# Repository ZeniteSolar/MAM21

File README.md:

# MAM21
**M**ódulo de **A**cionamento do **M**otor 2021

Embarcação Guarapuvu II

Equipe Zênite Solar

### About
High current >150A Electronic Speed Controller for **[ME0909](https://www.electricmotorsport.com/me0909-pmdc-motor-12-48v-4-hp-cont-12-8-hp-pk.html)** motor, with CANBus.

### Images

### Sobre
Este módulo é responsável por realizar o acionamento de um motor de imã permanente, controlando sua velocidade e sentido de rotação.

### Requisitos de projeto

1. **Acionamento do motor**
   - Permitir o acionamento nos dois sentidos de rotação
   - Permitir o controle em malha fechada
     - Corrente/Torque
     - Tensão/RPM

2. **Proteções**
   - Sobre-temperatura do motor
   - Sobre-temperatura do acionamento
   - Sobre-tensão de entrada
   - Sobre-corrente de saída
   - Falha de comunicação
   - Desconexão dos mosfets de potência
     - Garantir que os mosfets permaneçam desligados se a placa de controle for removida
   - Lógica para início de funcionamento
     - O motor só pode ser acionado se o procedimento de início for seguido na sequência correta
       - Dead man`s switch conectado
       - Sistema elétrico ativado
       - Potenciômetro em zero
       - Chave do motor ligada

3. **Interfaces**
   - Ser controlado pela rede CANBUS implementada na embarcação
   - Sinalização por meio de LEDs
   - Permitir debug pela serial

### Abordagens

Especificações do conversor

| Tensão de Entrada | 20 ~ 60 V |
| ----------------: | :-------- |
|   Tensão de Saída | 0 ~ 48V   |
| Corrente de Saída | 150 A     |
|        Eficiência | > 80%     |

Dados os requisitos e especificações apresentadas anteriormente, foi definido que a topologia utilizada será um conversor ***chopper***, por não haver necessidade de elevação de tensão e por este permitir a variação da tensão média na carga mantendo uma boa eficiência. 

Em um motor DC, a inversão de seu sentido de rotação é feita com a inversão da polaridade, obtida conforme a lógica de acionamento das chaves da ponte H. Uma característica da ponte H completa é que além da inversão de polaridade é possível criar lógicas de acionamento para frear o motor. Importante lembrar que **AS CHAVES DO MESMO BRAÇO NUNCA DEVEM SER ACIONADAS AO MESMO TEMPO**, sob pena de destruição das chaves ou danos ao sistema elétrico da embarcação.

Para que seja possível o monitoramento dos parâmetros do motor e para fechar a malha de controle, precisarão ser empregados sensores para o monitoramento da corrente e rotação do motor. O diagrama abaixo apresenta a topologia utilizada para o acionamento.

O motor utilizado pela embarcação é o **[ME0909](https://www.electricmotorsport.com/me0909-pmdc-motor-12-48v-4-hp-cont-12-8-hp-pk.html)**. Este motor possui tensão de operação de 12 ~ 48V e 4,8 kW de potência nominal.

A rede CAN utilizada será a já implementada atualmente.

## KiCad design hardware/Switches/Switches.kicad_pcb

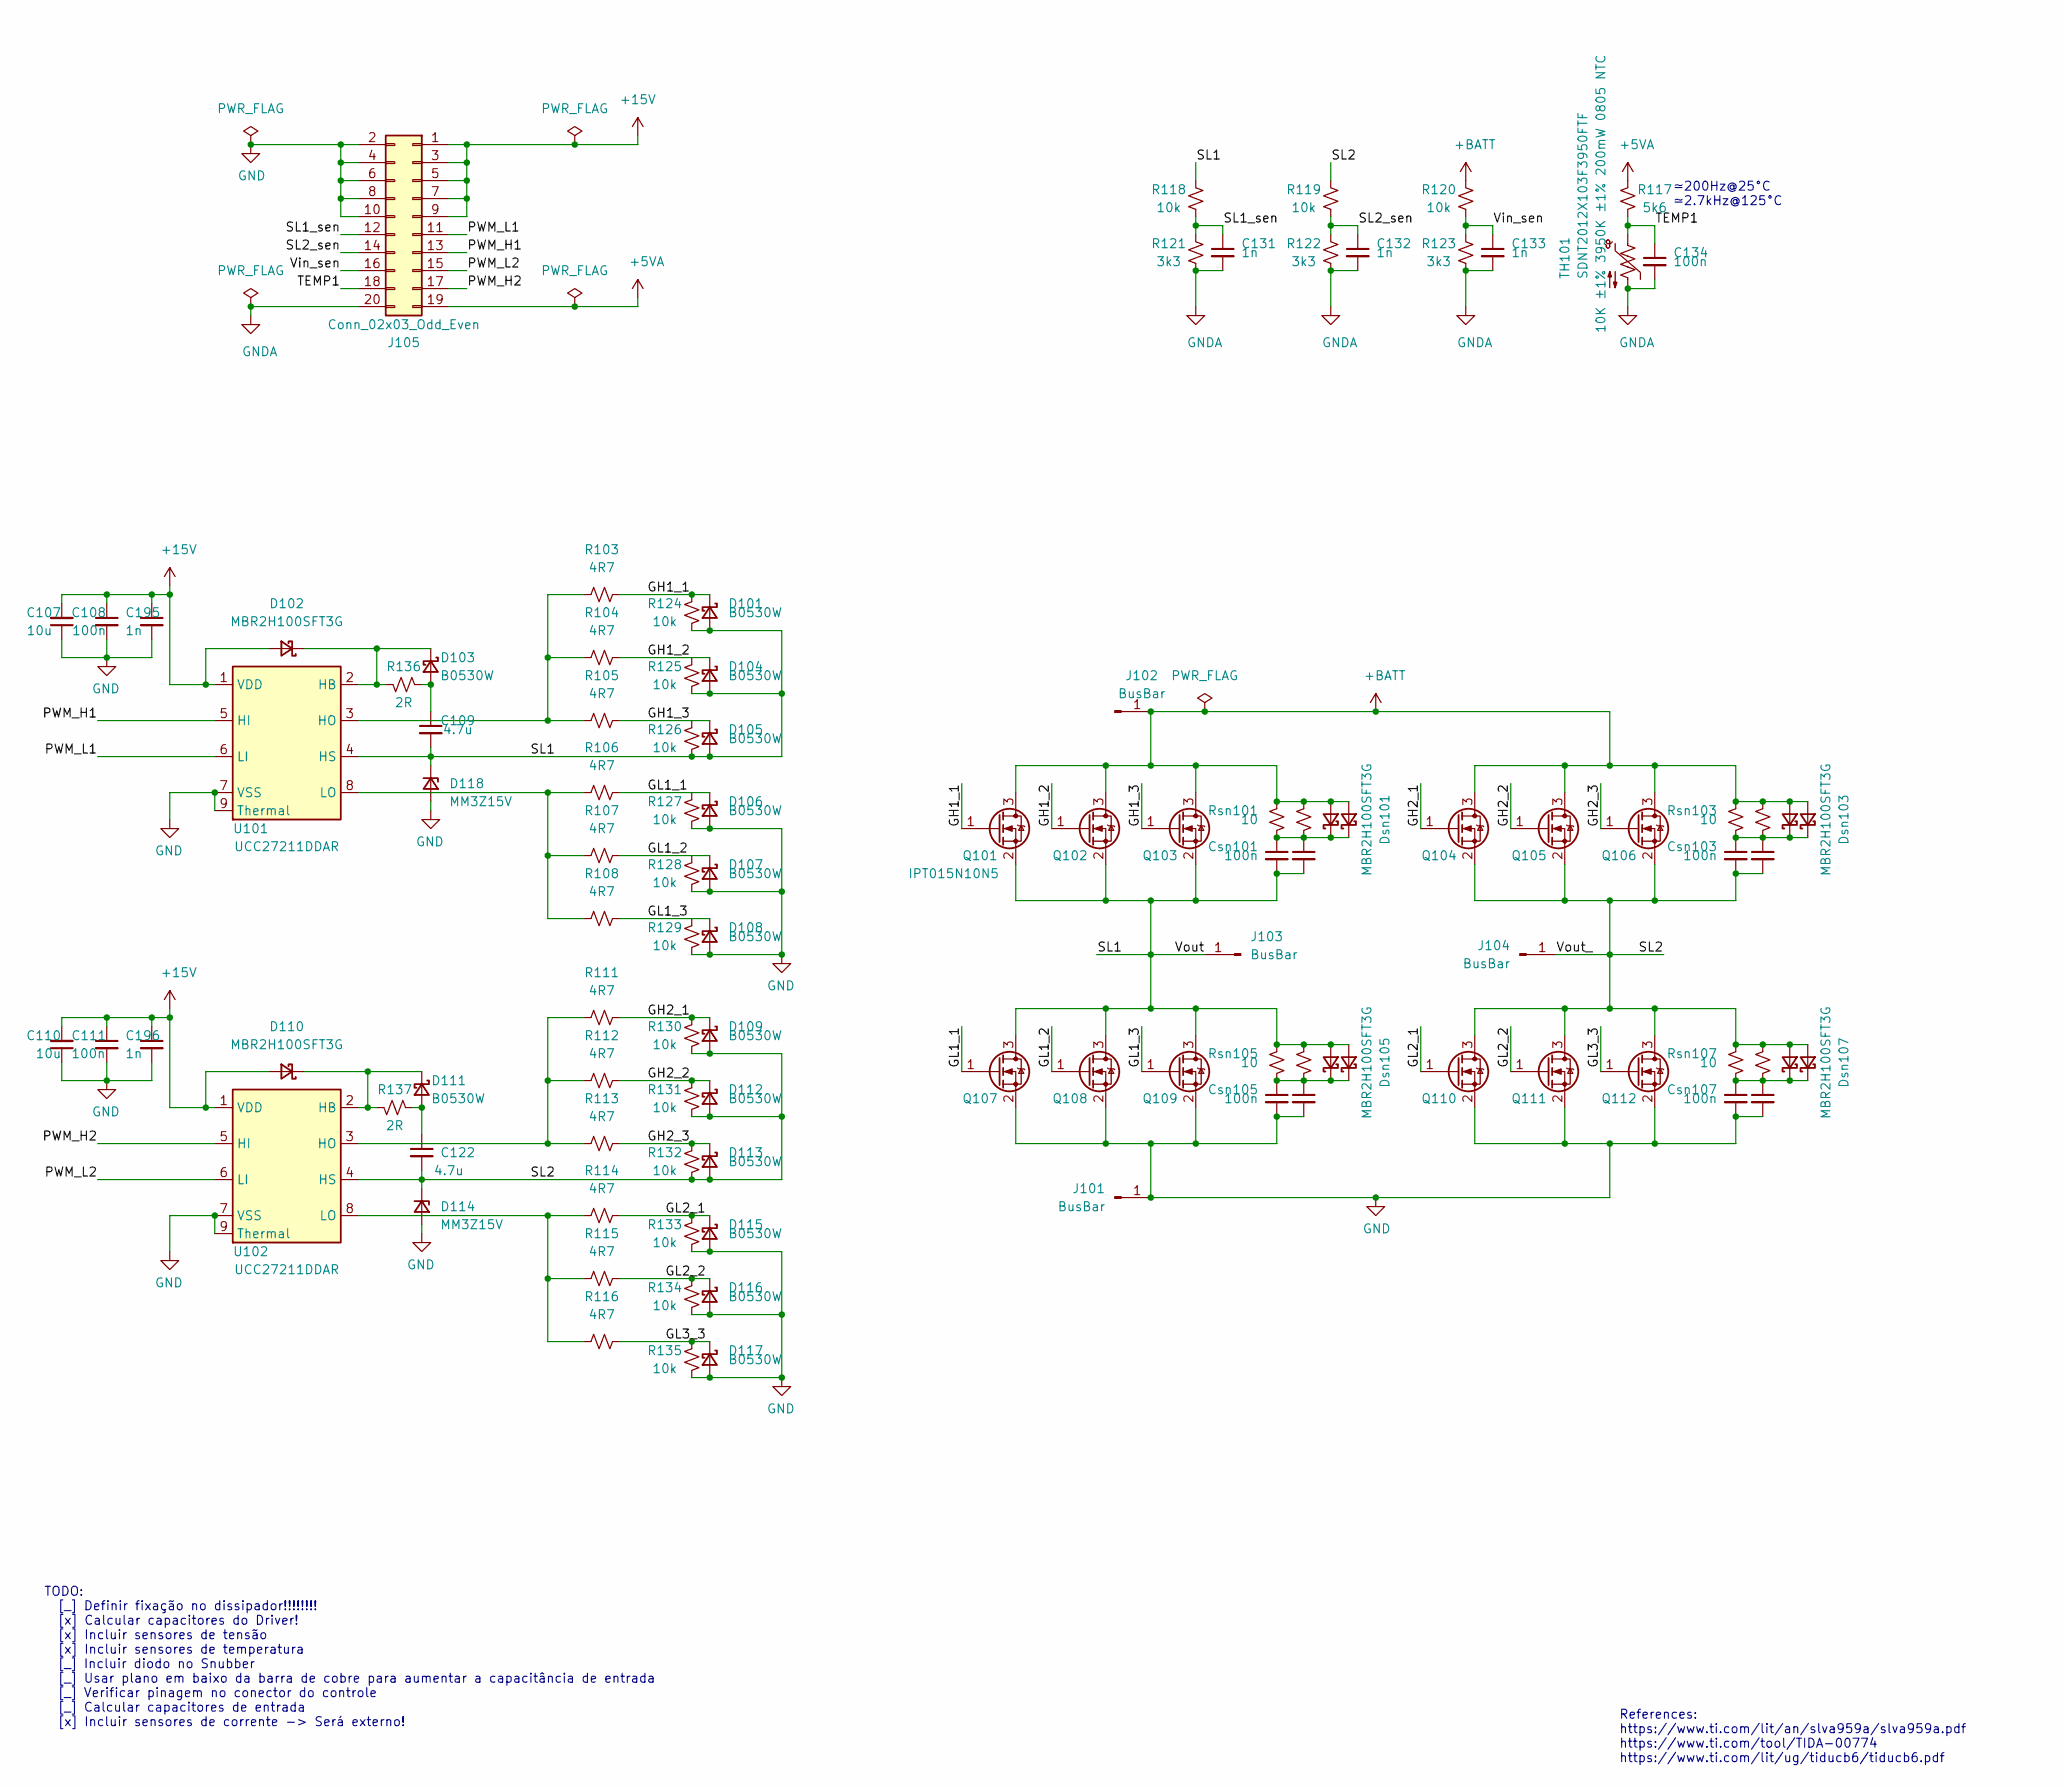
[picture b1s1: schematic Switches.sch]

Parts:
C107, C110: 10u; C_1210_3225Metric_Pad1.33x2.70mm_HandSolder
C108, C111: 100n; C_0805_2012Metric_Pad1.18x1.45mm_HandSolder
C109, C122: 4.7u; C_1210_3225Metric_Pad1.33x2.70mm_HandSolder
C131, C132, C133, C195, C196: 1n; C_0603_1608Metric_Pad1.08x0.95mm_HandSolder
C134: 100n; C_0603_1608Metric_Pad1.08x0.95mm_HandSolder
Csn101, Csn103, Csn105, Csn107: 100n; C_1210_3225Metric_Pad1.33x2.70mm_HandSolder
Csn102, Csn104, Csn106, Csn108: NC; C_1210_3225Metric_Pad1.33x2.70mm_HandSolder
D101, D103, D104, D105, D106, D107, D108, D109, D111, D112, D113, D115, D116, D117: B0530W; D_SOD-123F
D102, D110: MBR2H100SFT3G; D_SOD-123F
D114, D118: MM3Z15V; D_SOD-323
Dsn101, Dsn103, Dsn105, Dsn107: MBR2H100SFT3G; D_SOD-123F
Dsn102, Dsn104, Dsn106, Dsn108: NC; D_SOD-123F
J101, J102: BusBar; BusBar1
J103, J104: BusBar; BusBar2
J105: Conn_02x03_Odd_Even; PinHeader_2x10_P1.27mm_Vertical_SMD
Q101, Q102, Q103, Q104, Q105, Q106, Q107, Q108, Q109, Q110, Q111, Q112: IPT015N10N5; Infineon_PG-HSOF-8-1_ThermalVias3
R103, R104, R105, R106, R107, R108, R111, R112, R113, R114, R115, R116: 4R7; R_0805_2012Metric_Pad1.20x1.40mm_HandSolder
R117: 5k6; R_0603_1608Metric_Pad0.98x0.95mm_HandSolder
R118, R119, R120, R124, R125, R126, R127, R128, R129, R130, R131, R132, R133, R134, R135: 10k; R_0603_1608Metric_Pad0.98x0.95mm_HandSolder
R121, R122, R123: 3k3; R_0603_1608Metric_Pad0.98x0.95mm_HandSolder
R136, R137: 2R; R_0603_1608Metric_Pad0.98x0.95mm_HandSolder
Rsn101, Rsn103, Rsn105, Rsn107: 10; R_1210_3225Metric_Pad1.30x2.65mm_HandSolder
Rsn102, Rsn104, Rsn106, Rsn108: NC; R_1210_3225Metric_Pad1.30x2.65mm_HandSolder
TH101: SDNT2012X103F3950FTF; R_0805_2012Metric_Pad1.20x1.40mm_HandSolder
U101, U102: UCC27211DDAR; SOIC-8-1EP_3.9x4.9mm_P1.27mm_EP2.514x3.2mm_ThermalVias

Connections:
+5VA: J105.19, R117.1
+15V: C107.2, C108.1, C110.2, C111.1, C195.1, C196.1, D102.2 (A), D110.2 (A), J105.1, J105.3, J105.5, J105.7, J105.9, U101.1 (VDD), U102.1 (VDD)
+BATT: Dsn101.2 (A), Dsn102.2 (A), Dsn103.2 (A), Dsn104.2 (A), J102.1, Q101.3 (D), Q102.3 (D), Q103.3 (D), Q104.3 (D), Q105.3 (D), Q106.3 (D), R120.1, Rsn101.1, Rsn102.1, Rsn103.1, Rsn104.1
/GH1_1: D101.1 (K), Q101.1 (G), R103.1, R124.2
/GH1_2: D104.1 (K), Q102.1 (G), R104.1, R125.2
/GH1_3: D105.1 (K), Q103.1 (G), R105.1, R126.2
/GH2_1: D109.1 (K), Q104.1 (G), R111.1, R130.2
/GH2_2: D112.1 (K), Q105.1 (G), R112.1, R131.2
/GH2_3: D113.1 (K), Q106.1 (G), R113.1, R132.2
/GL1_1: D106.1 (K), Q107.1 (G), R106.1, R127.2
/GL1_2: D107.1 (K), Q108.1 (G), R107.1, R128.2
/GL1_3: D108.1 (K), Q109.1 (G), R108.1, R129.2
/GL2_1: D115.1 (K), Q110.1 (G), R114.1, R133.2
/GL2_2: D116.1 (K), Q111.1 (G), R115.1, R134.2
/GL3_3: D117.1 (K), Q112.1 (G), R116.1, R135.2
/PWM_H1: J105.13, U101.5 (HI)
/PWM_H2: J105.17, U102.5 (HI)
/PWM_L1: J105.11, U101.6 (LI)
/PWM_L2: J105.15, U102.6 (LI)
/SL1: C109.2, Csn101.2, Csn102.2, D101.2 (A), D104.2 (A), D105.2 (A), D118.1 (K), Dsn105.2 (A), Dsn106.2 (A), J103.1, Q101.2 (S), Q102.2 (S), Q103.2 (S), Q107.3 (D), Q108.3 (D), Q109.3 (D), R118.1, R124.1, R125.1, R126.1, Rsn105.1, Rsn106.1, U101.4 (HS)
/SL1_sen: C131.1, J105.12, R118.2, R121.1
/SL2: C122.2, Csn103.2, Csn104.2, D109.2 (A), D112.2 (A), D113.2 (A), D114.1 (K), Dsn107.2 (A), Dsn108.2 (A), J104.1, Q104.2 (S), Q105.2 (S), Q106.2 (S), Q110.3 (D), Q111.3 (D), Q112.3 (D), R119.1, R130.1, R131.1, R132.1, Rsn107.1, Rsn108.1, U102.4 (HS)
/SL2_sen: C132.1, J105.14, R119.2, R122.1
/TEMP1: C134.1, J105.18, R117.2, TH101.1
/Vin_sen: C133.1, J105.16, R120.2, R123.1
GND: C107.1, C108.2, C110.1, C111.2, C195.2, C196.2, Csn105.2, Csn106.2, Csn107.2, Csn108.2, D106.2 (A), D107.2 (A), D108.2 (A), D114.2 (A), D115.2 (A), D116.2 (A), D117.2 (A), D118.2 (A), J101.1, J105.2, J105.4, J105.6, J105.8, J105.10, Q107.2 (S), Q108.2 (S), Q109.2 (S), Q110.2 (S), Q111.2 (S), Q112.2 (S), R127.1, R128.1, R129.1, R133.1, R134.1, R135.1, U101.7 (VSS), U101.9 (Thermal), U102.7 (VSS), U102.9 (Thermal)
GNDA: C131.2, C132.2, C133.2, C134.2, J105.20, R121.2, R122.2, R123.2, TH101.2
unnamed: C109.1, D103.2 (A), R136.2
unnamed: C122.1, D111.2 (A), R137.2
unnamed: Csn101.1, Csn102.1, Dsn101.1 (K), Dsn102.1 (K), Rsn101.2, Rsn102.2
unnamed: Csn103.1, Csn104.1, Dsn103.1 (K), Dsn104.1 (K), Rsn103.2, Rsn104.2
unnamed: Csn105.1, Csn106.1, Dsn105.1 (K), Dsn106.1 (K), Rsn105.2, Rsn106.2
unnamed: Csn107.1, Csn108.1, Dsn107.1 (K), Dsn108.1 (K), Rsn107.2, Rsn108.2
unnamed: D102.1 (K), D103.1 (K), R136.1, U101.2 (HB)
unnamed: D110.1 (K), D111.1 (K), R137.1, U102.2 (HB)
unnamed: R103.2, R104.2, R105.2, U101.3 (HO)
unnamed: R106.2, R107.2, R108.2, U101.8 (LO)
unnamed: R111.2, R112.2, R113.2, U102.3 (HO)
unnamed: R114.2, R115.2, R116.2, U102.8 (LO)

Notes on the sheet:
TODO: [_] Definir fixação no dissipador!!!!!!!! [x] Calcular capacitores do Driver! [x] Incluir sensores de tensão [x] Incluir sensores de temperatura [_] Incluir diodo no Snubber [_] Usar plano em baixo da barra de cobre para aumentar a capacitância de entrada [_] Verificar pinagem no conector do 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
References: https://www.ti.com/lit/an/slva959a/slva959a.pdf https://www.ti.com/tool/TIDA-00774 https://www.ti.com/lit/ug/tiducb6/tiducb6.pdf
≃200Hz@25°C ≃2.7kHz@125°C

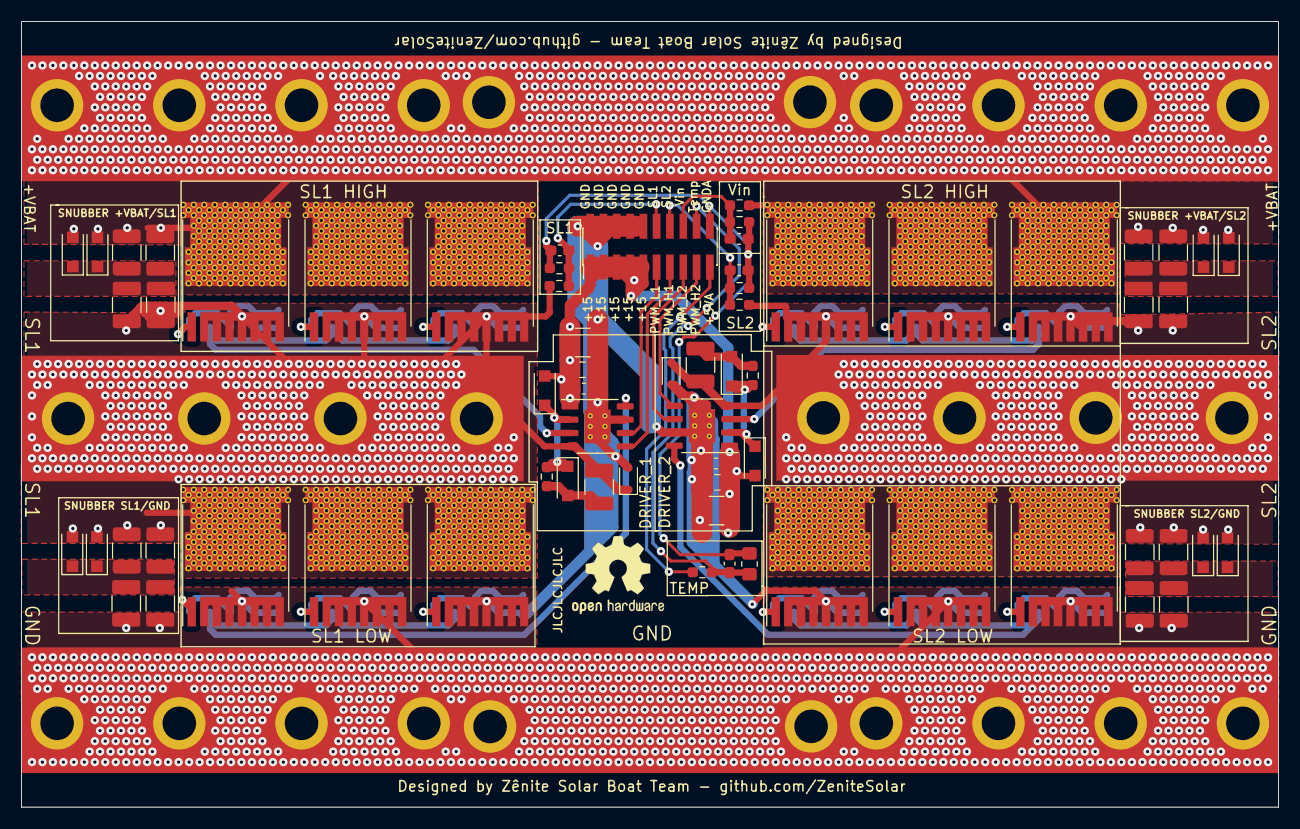
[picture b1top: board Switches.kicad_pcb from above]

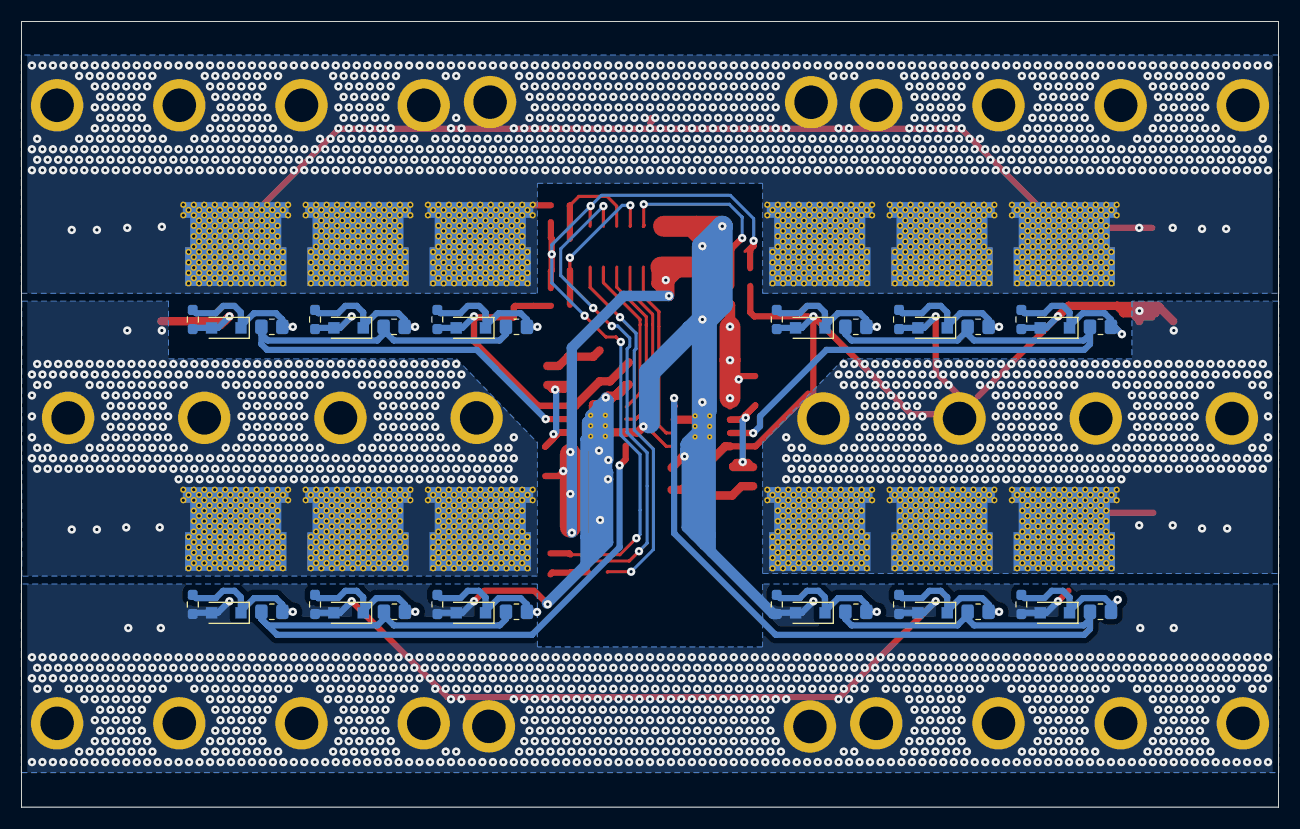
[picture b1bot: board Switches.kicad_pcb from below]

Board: 4 copper layers, 120.0 x 75.0 mm, 107 parts (36 on the bottom side), 39 nets.

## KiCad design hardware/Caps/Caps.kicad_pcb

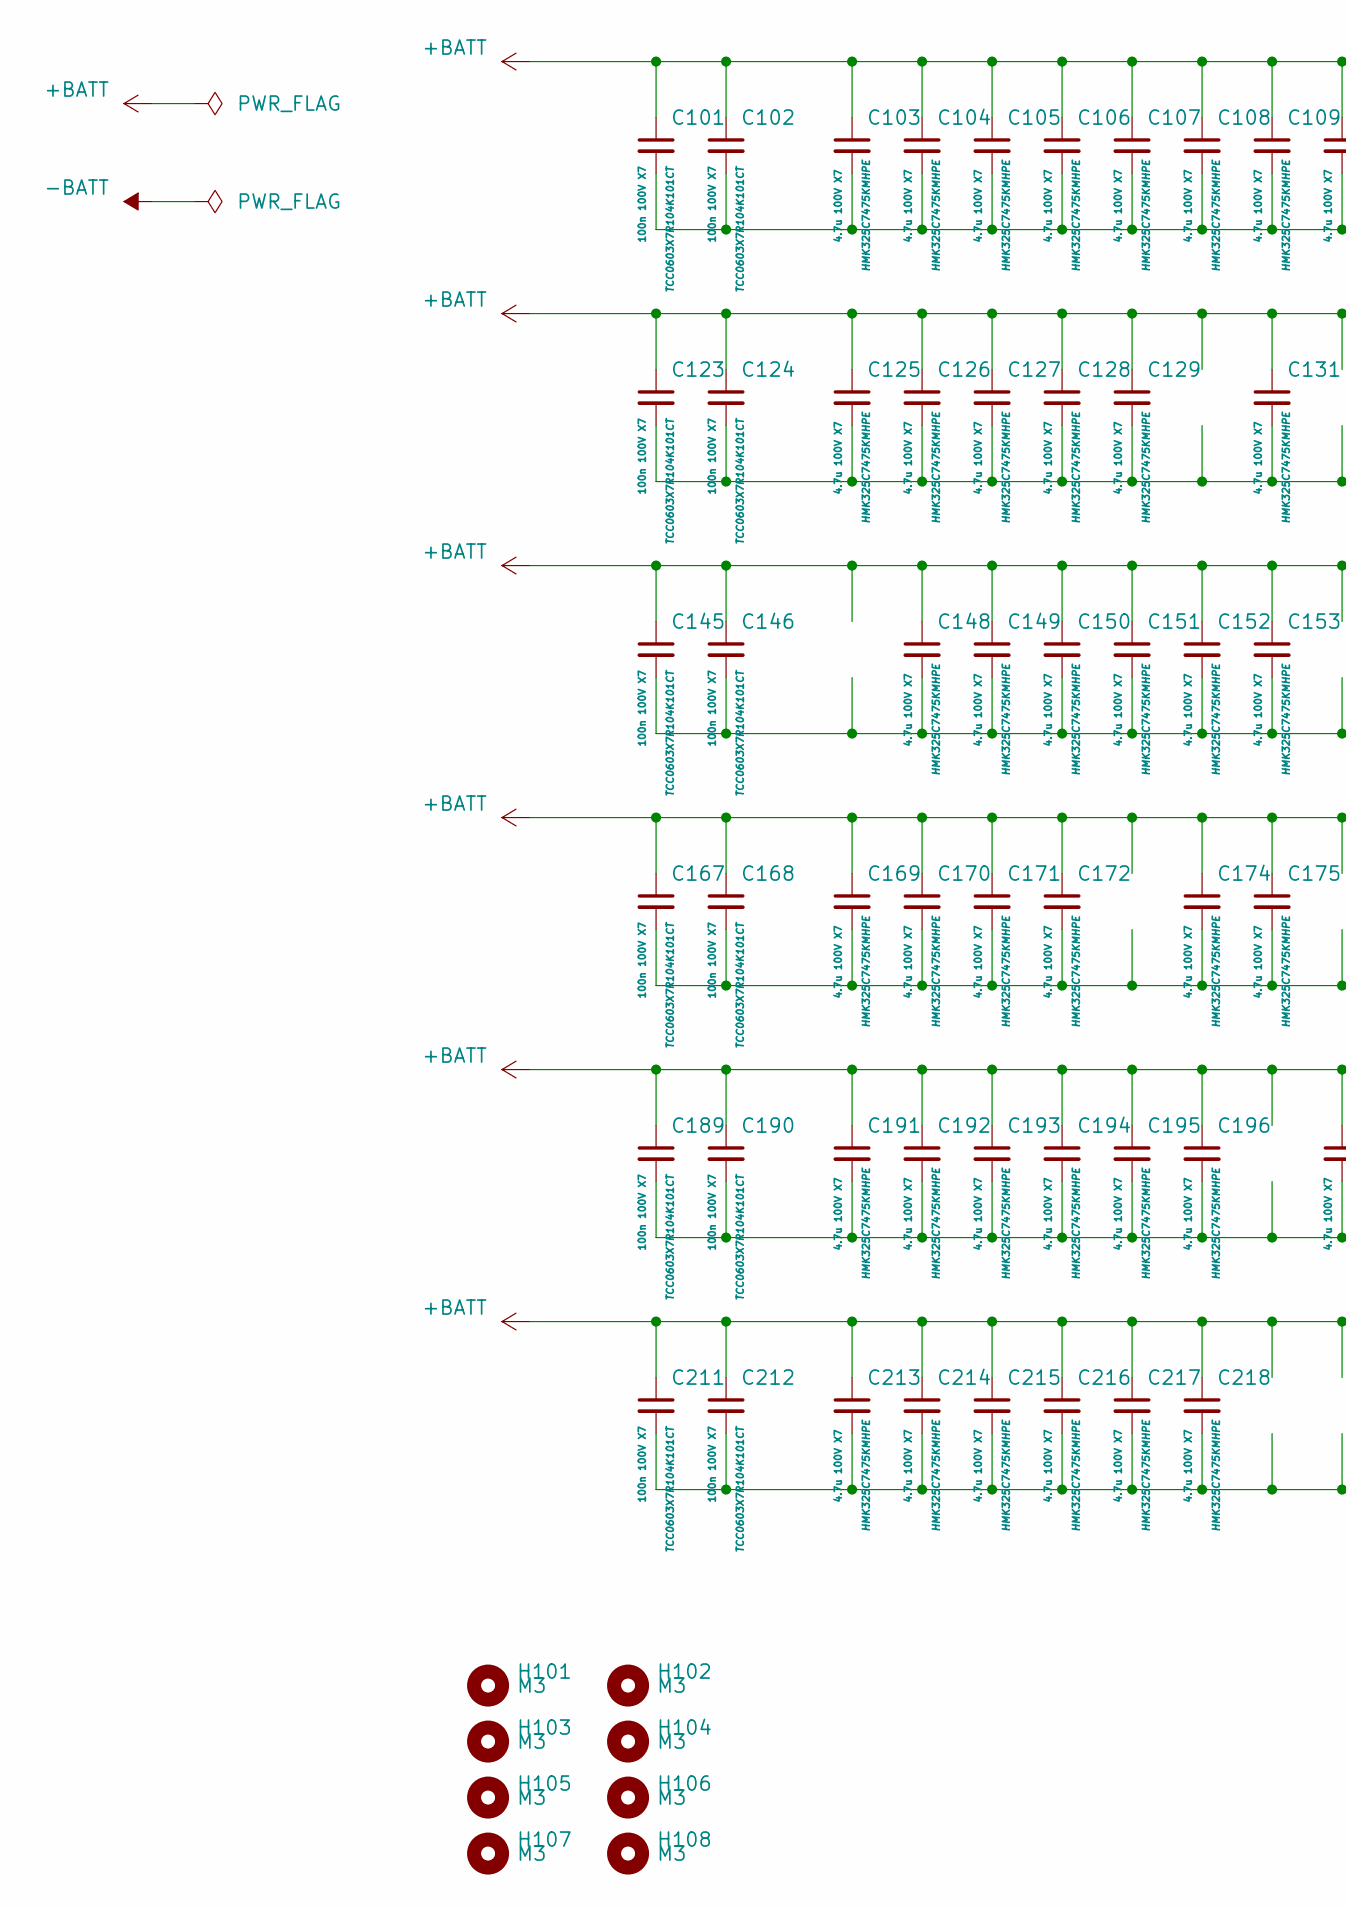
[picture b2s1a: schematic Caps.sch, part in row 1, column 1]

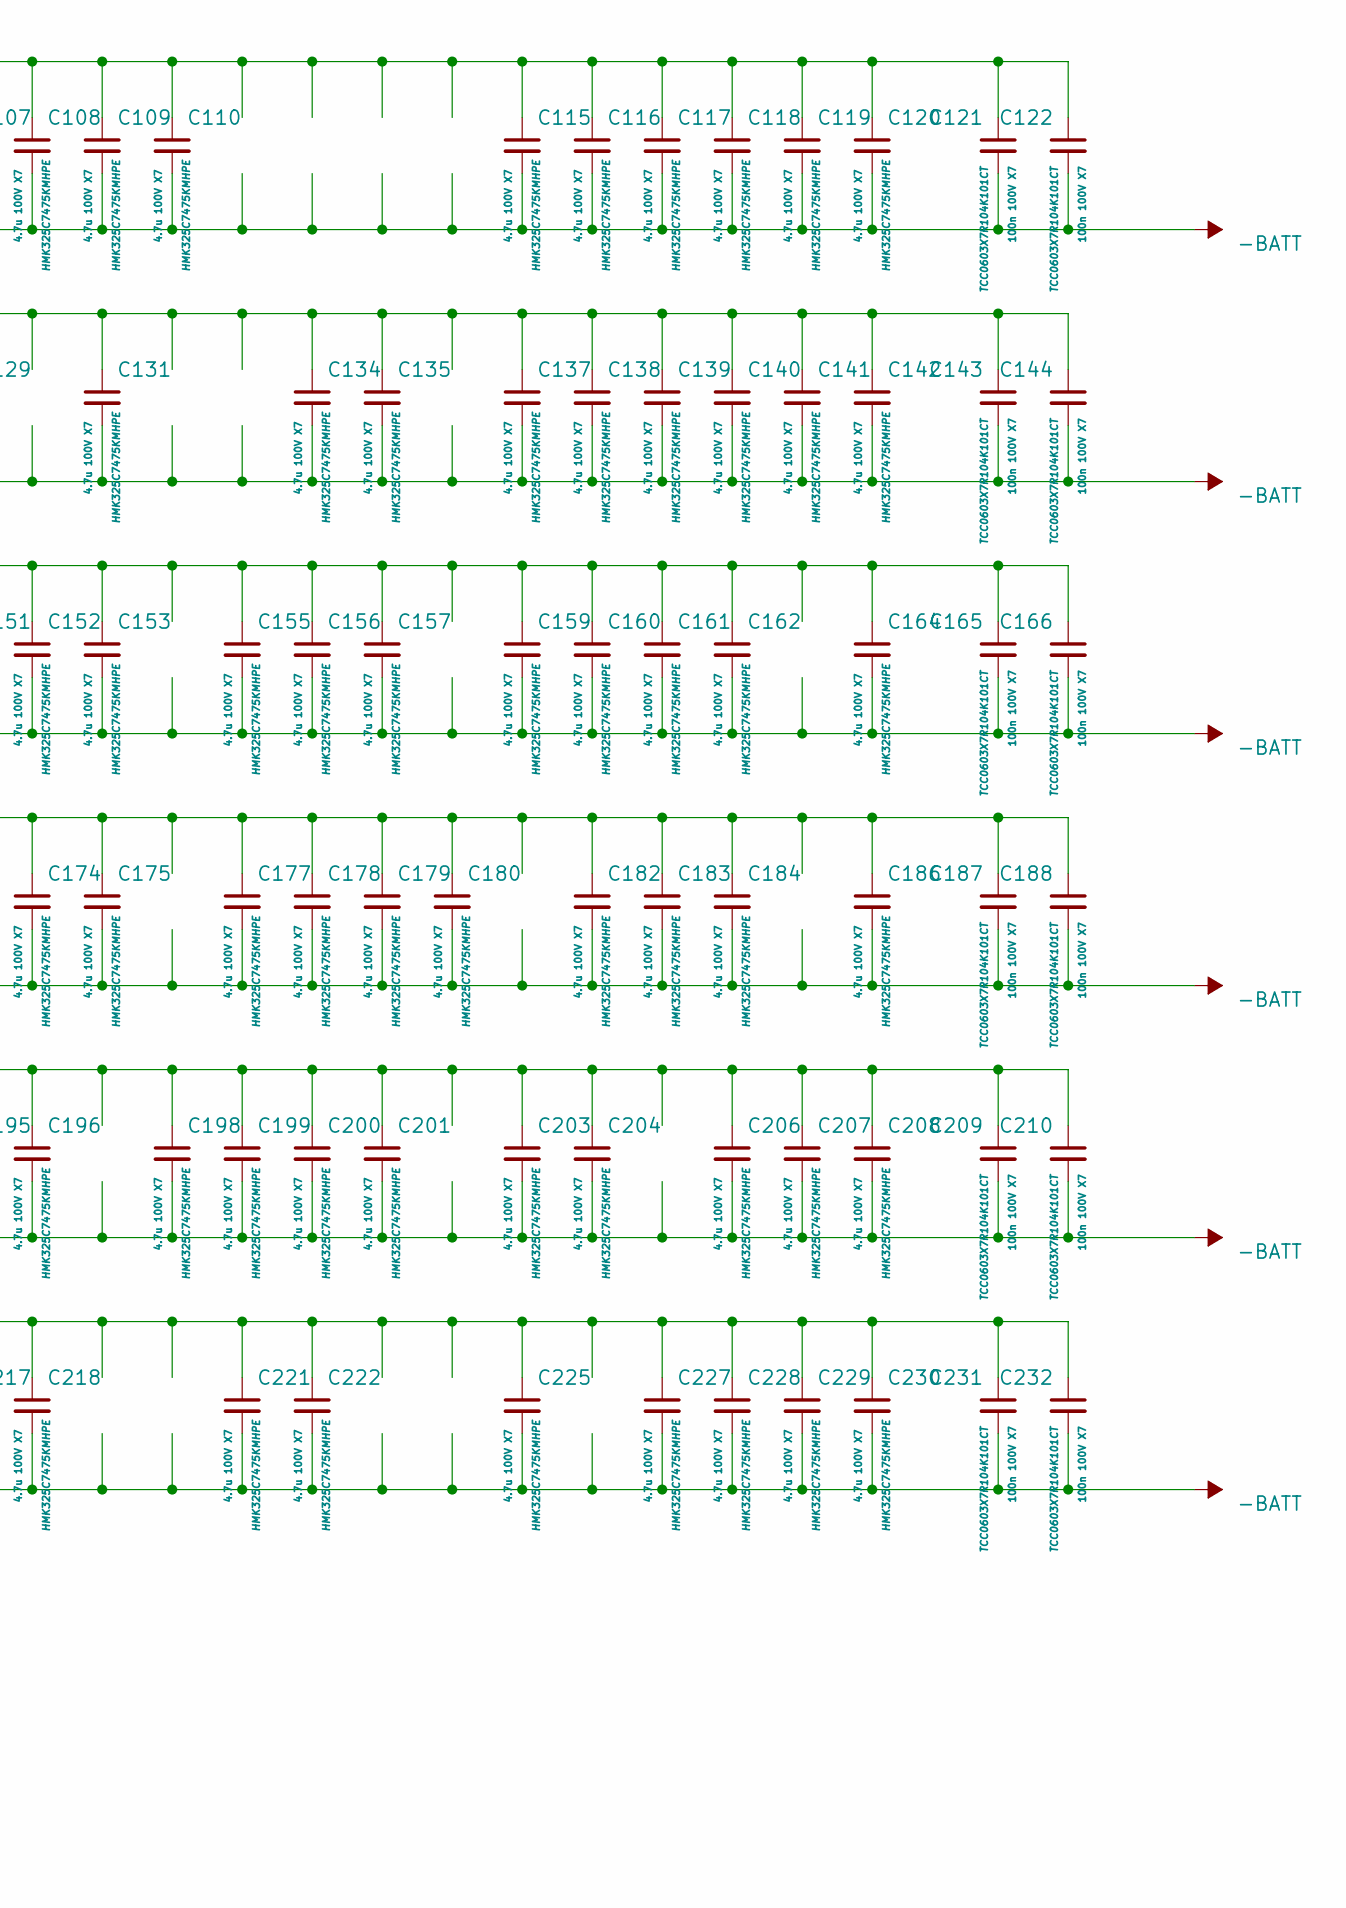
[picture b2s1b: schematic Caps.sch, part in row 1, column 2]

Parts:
C101, C102, C121, C122, C123, C124, C143, C144, C145, C146, C165, C166, C167, C168, C187, C188, C189, C190, C209, C210, C211, C212, C231, C232: 100n 100V X7; C_0603_1608Metric_Pad1.08x0.95mm_HandSolder; PartNumber TCC0603X7R104K101CT
C103, C104, C105, C106, C107, C108, C109, C110, C115, C116, C117, C118, C119, C120, C125, C126, C127, C128, C129, C131, C134, C135, C137, C138, C139, C140, C141, C142, C148, C149, C150, C151, C152, C153, C155, C156, C157, C159, C160, C161, C162, C164, C169, C170, C171, C172, C174, C175, C177, C178, C179, C180, C182, C183, C184, C186, C191, C192, C193, C194, C195, C196, C198, C199, C200, C201, C203, C204, C206, C207, C208, C213, C214, C215, C216, C217, C218, C221, C222, C225, C227, C228, C229, C230: 4.7u 100V X7; C_1210_3225Metric_Pad1.33x2.70mm_HandSolder; PartNumber HMK325C7475KMHPE
H101, H102, H103, H104, H105, H106, H107, H108: M3; MountingHole_3.2mm_M3

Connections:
+BATT: C101.1, C102.1, C103.1, C104.1, C105.1, C106.1, C107.1, C108.1, C109.1, C110.1, C115.1, C116.1, C117.1, C118.1, C119.1, C120.1, C121.1, C122.1, C123.1, C124.1, C125.1, C126.1, C127.1, C128.1, C129.1, C131.1, C134.1, C135.1, C137.1, C138.1, C139.1, C140.1, C141.1, C142.1, C143.1, C144.1, C145.1, C146.1, C148.1, C149.1, C150.1, C151.1, C152.1, C153.1, C155.1, C156.1, C157.1, C159.1, C160.1, C161.1, C162.1, C164.1, C165.1, C166.1, C167.1, C168.1, C169.1, C170.1, C171.1, C172.1, C174.1, C175.1, C177.1, C178.1, C179.1, C180.1, C182.1, C183.1, C184.1, C186.1, C187.1, C188.1, C189.1, C190.1, C191.1, C192.1, C193.1, C194.1, C195.1, C196.1, C198.1, C199.1, C200.1, C201.1, C203.1, C204.1, C206.1, C207.1, C208.1, C209.1, C210.1, C211.1, C212.1, C213.1, C214.1, C215.1, C216.1, C217.1, C218.1, C221.1, C222.1, C225.1, C227.1, C228.1, C229.1, C230.1, C231.1, C232.1
-BATT: C101.2, C102.2, C103.2, C104.2, C105.2, C106.2, C107.2, C108.2, C109.2, C110.2, C115.2, C116.2, C117.2, C118.2, C119.2, C120.2, C121.2, C122.2, C123.2, C124.2, C125.2, C126.2, C127.2, C128.2, C129.2, C131.2, C134.2, C135.2, C137.2, C138.2, C139.2, C140.2, C141.2, C142.2, C143.2, C144.2, C145.2, C146.2, C148.2, C149.2, C150.2, C151.2, C152.2, C153.2, C155.2, C156.2, C157.2, C159.2, C160.2, C161.2, C162.2, C164.2, C165.2, C166.2, C167.2, C168.2, C169.2, C170.2, C171.2, C172.2, C174.2, C175.2, C177.2, C178.2, C179.2, C180.2, C182.2, C183.2, C184.2, C186.2, C187.2, C188.2, C189.2, C190.2, C191.2, C192.2, C193.2, C194.2, C195.2, C196.2, C198.2, C199.2, C200.2, C201.2, C203.2, C204.2, C206.2, C207.2, C208.2, C209.2, C210.2, C211.2, C212.2, C213.2, C214.2, C215.2, C216.2, C217.2, C218.2, C221.2, C222.2, C225.2, C227.2, C228.2, C229.2, C230.2, C231.2, C232.2

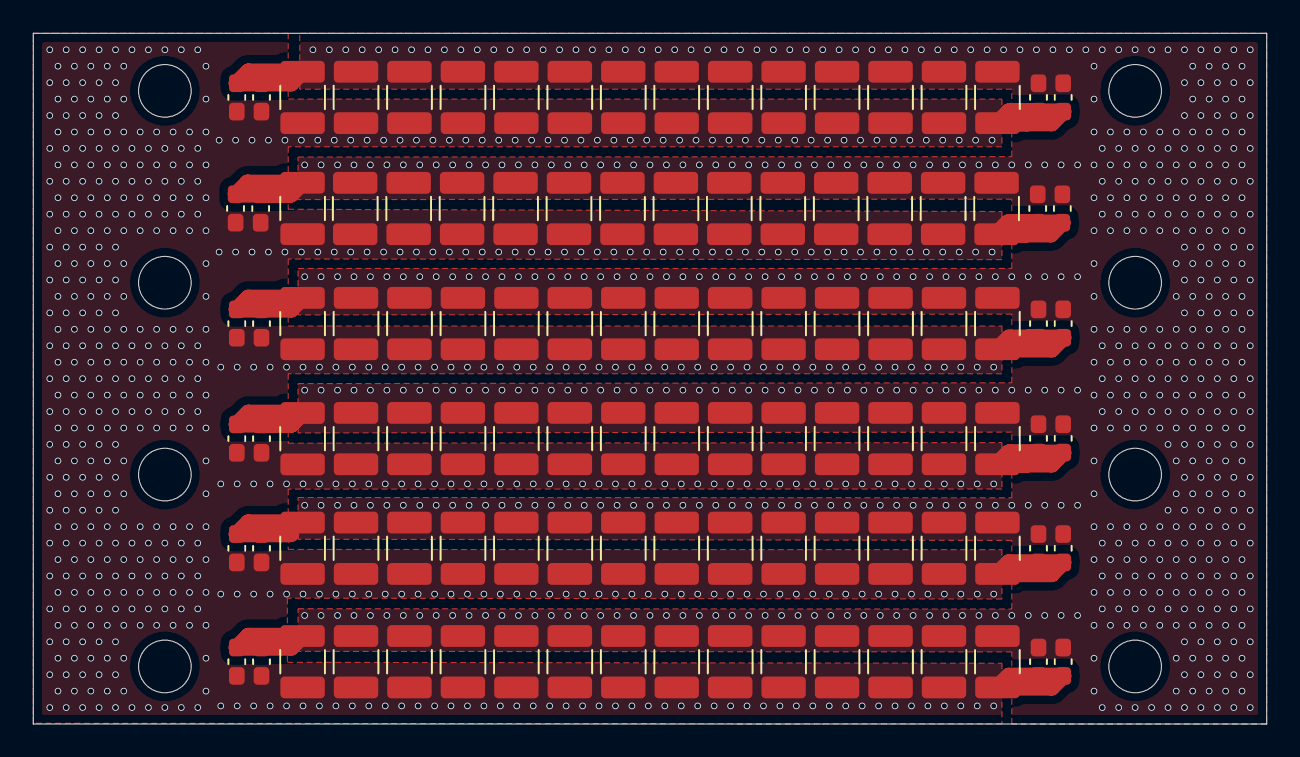
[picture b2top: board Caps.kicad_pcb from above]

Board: 2 copper layers, 75.0 x 42.0 mm, 116 parts (0 on the bottom side), 2 nets.

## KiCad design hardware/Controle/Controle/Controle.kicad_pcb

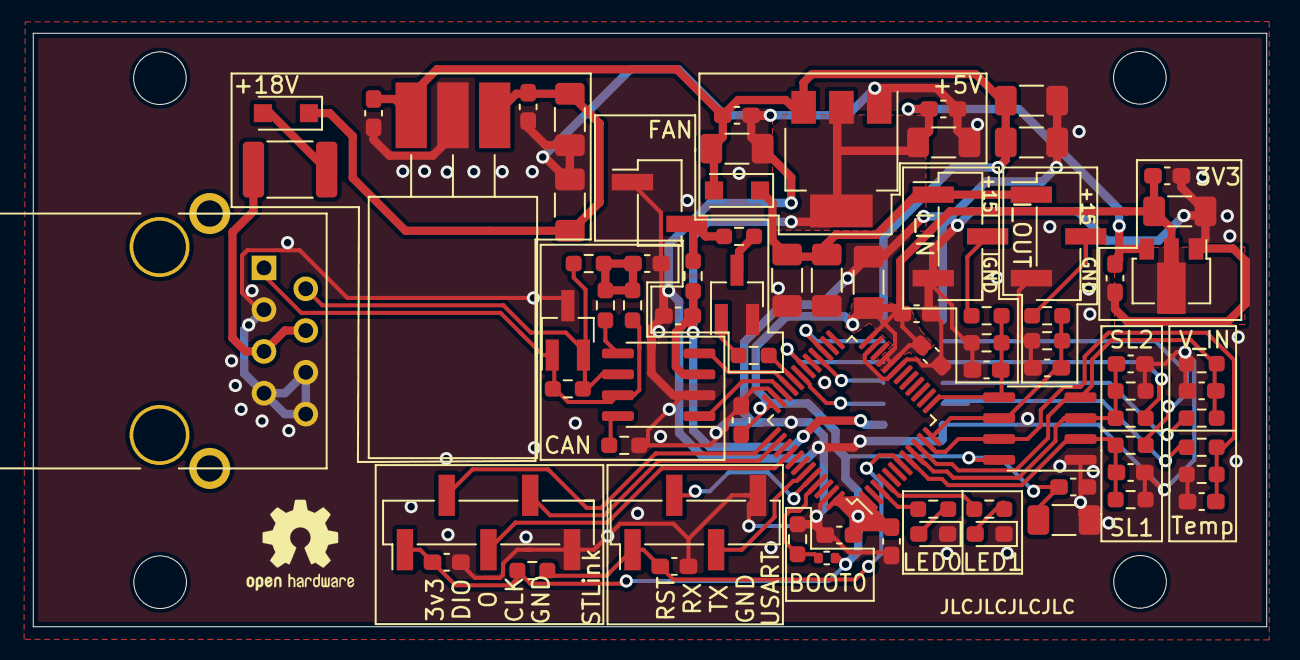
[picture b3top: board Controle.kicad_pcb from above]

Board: 2 copper layers, 75.0 x 36.1 mm, 82 parts (1 on the bottom side), 46 nets.

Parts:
C1, C2, C3, C4, C5, C6, C7, C12, C102, C103, C104: 4.7u; C_1206_3216Metric_Pad1.33x1.80mm_HandSolder
C8, C9, C10, C11, C101, C201, C401, C402, C403, C404, C405, C406, C503, C504, C604, C607: 100n; C_0603_1608Metric_Pad1.08x0.95mm_HandSolder
C202: 4.7n; C_0603_1608Metric_Pad1.08x0.95mm_HandSolder
C601, C602, C603: 1n; C_0603_1608Metric_Pad1.08x0.95mm_HandSolder
C605, C606: NC; C_0603_1608Metric_Pad1.08x0.95mm_HandSolder
D101, D102: B0530W; D_SOD-123F
D201: pesd1can; SOT-23_Handsoldering
D501: B; LED_0603_1608Metric_Pad1.05x0.95mm_HandSolder
D502: G; LED_0603_1608Metric_Pad1.05x0.95mm_HandSolder
F101: 1A; Fuse_1812_4532Metric_Pad1.30x3.40mm_HandSolder
H101, H102, H103, H104: MountingHole; MountingHole_3.2mm_M3
J101: USART; PinHeader_1x04_P2.54mm_Vertical_SMD_Pin1Left
J102: ST_LINK; PinHeader_1x05_P2.54mm_Vertical_SMD_Pin1Left
J103: FAN; PinHeader_1x02_P2.54mm_Vertical_SMD_Pin1Left
J105, J106: Iin_sen; PinHeader_1x03_P2.54mm_Vertical_SMD_Pin1Left
J107: Driver-Sense; PinSocket_2x10_P1.27mm_Vertical_SMD
J301: RJ45; RJ45_YH59_01
Q101: BCV27; SOT-23_Handsoldering
R101, R102: 100R; R_0603_1608Metric_Pad0.98x0.95mm_HandSolder
R103, R501, R502, R503, R505, R601, R602, R603: 10k; R_0603_1608Metric_Pad0.98x0.95mm_HandSolder
R201: 4k7; R_0603_1608Metric_Pad0.98x0.95mm_HandSolder
R202: 1k; R_0603_1608Metric_Pad0.98x0.95mm_HandSolder
R203: 300; R_0603_1608Metric_Pad0.98x0.95mm_HandSolder
R204, R205: 60; R_0603_1608Metric_Pad0.98x0.95mm_HandSolder
R504: BOOT0; R_0402_1005Metric
R604: 0R; R_0603_1608Metric_Pad0.98x0.95mm_HandSolder
R605, R606, R610, R611, R612: NC; R_0603_1608Metric_Pad0.98x0.95mm_HandSolder
R607, R608, R609: 3k3; R_0603_1608Metric_Pad0.98x0.95mm_HandSolder
U201: MCP2561-E-SN; SOIC-8_3.9x4.9mm_P1.27mm
U401: AMS1117-3.3; SOT-89-3
U402: AMS1117-5; SOT-223-3_TabPin2
U403: K78L15-1000R3; TO-220-3_Horizontal_Tabless_SMD
U501: STM32G431CBT6; LQFP-48_7x7mm_P0.5mm
U601: TL7726IDR; SOIC-8_3.9x4.9mm_P1.27mm

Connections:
+3V3: C2.2, C7.2, C8.2, C9.2, C10.2, C11.2, C12.2, C101.2, C401.2, C504.2, C607.2, J102.1, R501.2, R504.1, U401.2, U501.1, U501.20, U501.21, U501.24, U501.36, U501.48, U601.8
+5V: C3.2, C201.2, C402.2, C403.2, J107.19, R103.2, U201.3, U401.3, U402.2
+15V: C1.2, C4.2, C104.2, C404.2, C405.2, D102.2, J107.1, J107.3, J107.5, J107.7, J107.9, U402.3, U403.3
/Iin_sen: J106.2, R605.2
/Iout_sen: J105.2, R606.2
/PWM_H1: J107.13, U501.30
/PWM_H2: J107.17, U501.31
/PWM_L1: J107.11, U501.27
/PWM_L2: J107.15, U501.28
/Powersupply/+18V: C5.2, C6.2, C406.2, D101.1, U403.1
/SL1_sen: J107.12, R601.2
/SL2_sen: J107.14, R602.2
/STM32/ADC1_IN0: C601.1, R601.1, R607.2, U501.8, U601.2
/STM32/ADC1_IN1: C602.1, R602.1, R608.2, U501.9, U601.3
/STM32/ADC1_IN2: C603.1, R603.1, R609.2, U501.10, U601.4
/STM32/ADCX_IN3: C604.1, R604.1, R610.2, U501.11, U601.7
/STM32/ADCX_IN4: C605.1, R605.1, R611.2, U501.12, U601.6
/STM32/ADCX_IN5: C606.1, R606.1, R612.2, U501.13, U601.5
/STM32/BOOT0: R504.2, R505.1, U501.45
/STM32/CAN_RX: U201.4, U501.33
/STM32/CAN_TX: U201.1, U501.34
/STM32/FAN: R102.1, U501.32
/STM32/LED0: R502.1, U501.3
/STM32/LED1: R503.1, U501.4
/STM32/RESET: C503.2, J101.1, R501.1, U501.7
/STM32/SWCLK: J102.4, U501.38
/STM32/SWDIO: J102.2, U501.37
/STM32/SWO: J102.3, U501.40
/STM32/USART3_RX: J101.2, U501.44
/STM32/USART3_TX: J101.3, U501.43
/Temp1: J107.18, R604.2
/Vin_sen: J107.16, R603.2
/canbus/CAN_H: D201.1, J301.1, R202.2, R204.2, U201.7
/canbus/CAN_L: D201.2, J301.2, R202.1, R205.1, U201.6
/canbus_connector/CAN_18V: F101.2, J301.4, J301.5
GND: C1.1, C2.1, C3.1, C4.1, C5.1, C6.1, C7.1, C8.1, C9.1, C10.1, C11.1, C12.1, C101.1, C102.1, C103.1, C104.1, C201.1, C202.2, C401.1, C402.1, C403.1, C404.1, C405.1, C406.1, C503.1, C504.1, C601.2, C602.2, C603.2, C604.2, C605.2, C606.2, C607.1, D201.3, D501.1, D502.1, J101.4, J102.5, J103.1, J105.3, J106.3, J107.2, J107.4, J107.6, J107.8, J107.10, J107.20, J301.3, J301.6, J301.7, J301.8, Q101.2, R201.2, R505.2, R607.1, R608.1, R609.1, R610.1, R611.1, R612.1, U201.2, U401.1, U402.1, U403.2, U501.19, U501.23, U501.35, U501.47, U601.1
unnamed: C102.2, C103.2, D102.1, J105.1, J106.1
unnamed: C202.1, R203.1, R204.1, R205.2
unnamed: D101.2, F101.1
unnamed: D501.2, R502.2
unnamed: D502.2, R503.2
unnamed: J103.2, R101.2, R103.1
unnamed: Q101.1, R102.2
unnamed: Q101.3, R101.1
unnamed: R201.1, U201.8
unnamed: R203.2, U201.5
